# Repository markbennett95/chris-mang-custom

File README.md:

# Custom Dual OD - Chris Mang

Custom dual drive in a 1590BB featuring a Zendrive on one side, and a modified bluesbreaker on the other.

## v1.0.0-build
1590BB encl. Works with `1590BB-2` of the [Dual Effect Order Switching Board](https://github.com/markbennett95/dual-effect-order-switching-board). Zendrive schematic is unchanged, using the "version" switch and a DG412. The Bluesbreaker is a pretty straight up clone with added clean blend.

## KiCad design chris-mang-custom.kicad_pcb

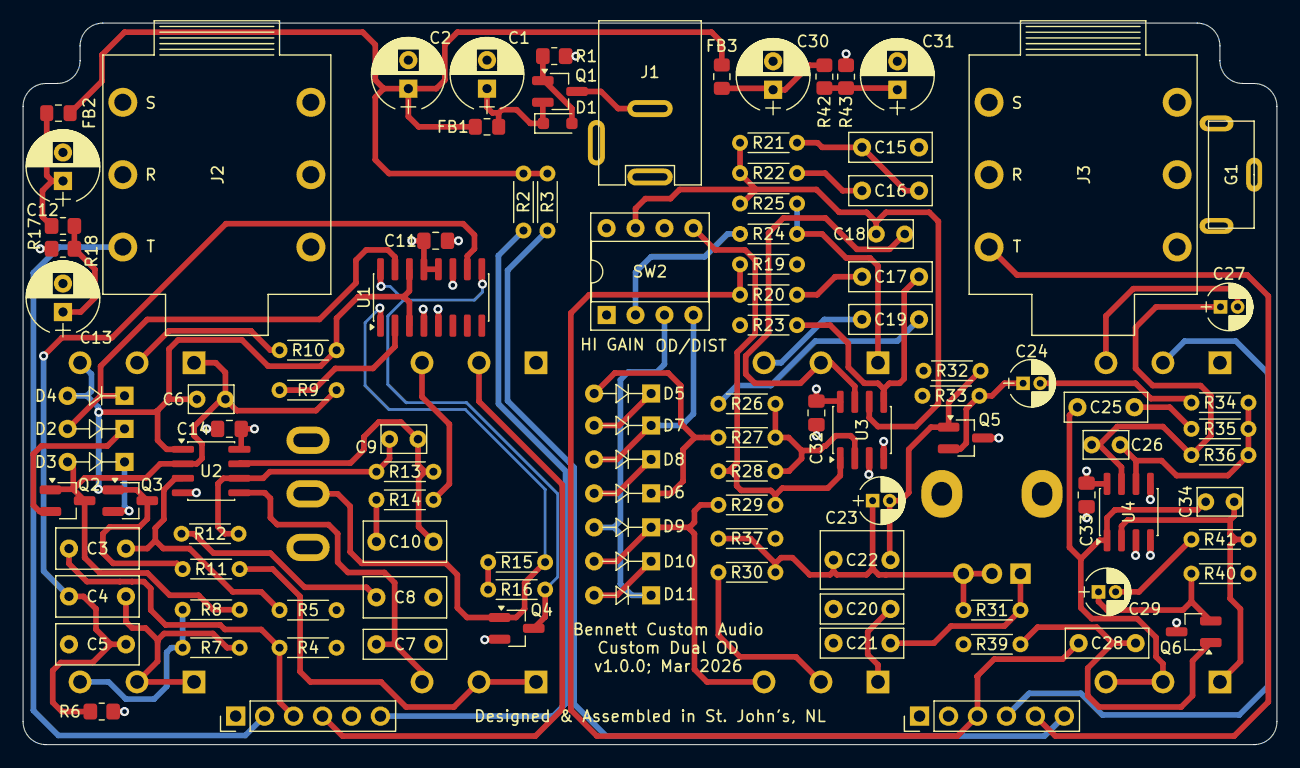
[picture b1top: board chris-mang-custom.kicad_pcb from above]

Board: 4 copper layers, 110.0 x 63.3 mm, 117 parts (1 on the bottom side), 72 nets.

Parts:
C1, C2: 100uF; CP_Radial_D6.3mm_P2.50mm
C3: 0.47u; C_Film_L7.2mm_W3.5mm_P5.00mm
C4, C5: 0.22u; C_Film_L7.2mm_W3.5mm_P5.00mm
C6, C18, C34: 100p; C_Ceramic_L4.0mm_W2.5mm_P2.50mm
C7: 3.3nF; C_Film_L7.2mm_W2.5mm_P5.00mm
C8: 0.22uF; C_Film_L7.2mm_W3.5mm_P5.00mm
C9: 470p; C_Ceramic_L4.0mm_W2.5mm_P2.50mm
C10: 0.47uF; C_Film_L7.2mm_W3.5mm_P5.00mm
C11: 1u; C_0805_2012Metric_Pad1.18x1.45mm_HandSolder
C12, C13, C30, C31: 100u; CP_Radial_D6.3mm_P2.50mm
C14, C32, C33: 100n; C_0805_2012Metric_Pad1.18x1.45mm_HandSolder
C15, C16, C17, C20, C21, C28: 10n; C_Film_L7.2mm_W2.5mm_P5.00mm
C19: 0.1u; C_Film_L7.2mm_W2.5mm_P5.00mm
C22: 1u; C_Film_L7.2mm_W5.00mm_P5.00mm
C23: 1u; CP_Radial_D4.0mm_P1.50mm
C24, C27, C29: 10u; CP_Radial_D4.0mm_P1.50mm
C25: 47n; C_Film_L7.2mm_W2.5mm_P5.00mm
C26: 47p; C_Ceramic_L4.0mm_W2.5mm_P2.50mm
D1: 9V1 Zener; D_SOD-323_HandSoldering
D2, D3, D4, D11: 1N5711; Diode_DO-35_P5.00mm
D5, D6, D7, D8, D9, D10: 1N4148; Diode_DO-35_P5.00mm
FB1, FB2, FB3: FerriteBead_Small; L_0805_2012Metric_Pad1.15x1.40mm_HandSolder
G1: GNDSpring; Keystone_628
J1: Barrel_Jack_Switch; DC_Jack_DC005
J2, J3: AudioJack_TRS; Rean_NYS215
J4, J5: Conn_01x06; Pin_Header_Straight_1x06_Pitch2.54mm
Q1: Q_PMOS_GSD; SOT-23_Handsoldering
Q2, Q3, Q4: 2N7002; SOT-23_Handsoldering
Q5, Q6: BC848C; SOT-23_Handsoldering
R1, R17, R18, R42, R43: 10k; R_0805_2012Metric_Pad1.20x1.40mm_HandSolder
R2, R3: 22k; R_L3.6mm_D1.6mm_P5.00mm_Horizontal
R4: 2.2M; R_L3.6mm_D1.6mm_P5.00mm_Horizontal
R5: 470k; R_L3.6mm_D1.6mm_P5.00mm_Horizontal
R6: 10M; R_0805_2012Metric_Pad1.20x1.40mm_HandSolder
R7, R10, R11, R13, R20, R26, R33, R40, R41: 10k; R_L3.6mm_D1.6mm_P5.00mm_Horizontal
R8, R14, R29: 1k; R_L3.6mm_D1.6mm_P5.00mm_Horizontal
R9: 680k; R_L3.6mm_D1.6mm_P5.00mm_Horizontal
R12: 18k; R_L3.6mm_D1.6mm_P5.00mm_Horizontal
R15, R16, R31, R34, R35, R37: 100k; R_L3.6mm_D1.6mm_P5.00mm_Horizontal
R19, R23, R32, R39: 1M; R_L3.6mm_D1.6mm_P5.00mm_Horizontal
R21: 27k; R_L3.6mm_D1.6mm_P5.00mm_Horizontal
R22: 33k; R_L3.6mm_D1.6mm_P5.00mm_Horizontal
R24: 39k; R_L3.6mm_D1.6mm_P5.00mm_Horizontal
R25: 150k; R_L3.6mm_D1.6mm_P5.00mm_Horizontal
R27, R30: 6.8k; R_L3.6mm_D1.6mm_P5.00mm_Horizontal
R28: 220k; R_L3.6mm_D1.6mm_P5.00mm_Horizontal
R36: 180k; R_L3.6mm_D1.6mm_P5.00mm_Horizontal
RV1: 10kC; R_POT
RV2: 1MA; R_POT
RV3: 50kB; R_POT
RV4, RV8, RV9: 100kA; R_POT
RV5: 100kB; R_POT
RV6: 25kB; R_POT
RV7: 100kA; R_POT_9mm
SW1: SW_SPDT; SW_Toggle_SPDT_SolderLug
SW2: SW_DIP_SPDT_2pos; DIP-8_W7.62mm_Socket
U1: DG412xY; SOIC-16_3.9x9.9mm_P1.27mm
U2: OPA2134; SOIC-8_3.9x4.9mm_P1.27mm
U3: NJM4580; SOIC-8_3.9x4.9mm_P1.27mm
U4: TLV9352; SOIC-8_3.9x4.9mm_P1.27mm

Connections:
+9V: C2.1, FB1.2, FB2.1, FB3.1, R2.2, R3.2
/V+0: J4.6, R2.1
/V+1: J5.6, R3.1
/Zendrive/4.5V: C13.1, R5.1, R17.1, R18.2
/Zendrive/9V: C11.1, C12.1, C14.1, FB2.2, R15.2, R16.2, R17.2, U1.12 (VL), U1.13 (V+), U2.8 (V+)
/Zendrive/Q1D: Q4.3 (D), R16.1, U1.9, U1.16
/Zendrive/Q1G: Q4.1 (G), R15.1, SW1.2 (B), U1.1
/bluesbreaker-return: J5.4, RV8.2
/bluesbreaker-send: C28.1, J5.3, R19.2, R20.1
/bluesbreaker/4.5V: C20.1, C21.1, C31.1, R23.1, R32.1, R37.1, R39.1, R42.1, R43.2, SW2.6 (A), U3.3 (+), U4.3 (+), U4.5 (+)
/bluesbreaker/9V: C30.1, C32.1, C33.1, FB3.2, Q5.3 (C), Q6.3 (C), R42.2, U3.8 (V+), U4.8 (V+)
/bluesbreaker/sw2: R24.1, SW2.2 (D)
/bluesbreaker/sw3: D9.2 (A), D11.1 (K), SW2.3 (C)
/bluesbreaker/sw4: D7.1 (K), D8.2 (A), SW2.4 (D)
/bluesbreaker/sw5: R28.2, R29.1, SW2.5 (B), U3.1
/bluesbreaker/sw7: C18.1, R21.2, R22.2, R25.1, SW2.7 (B), U3.6 (-)
/input_jack: J2.1 (T), J4.2
/output_jack: J3.1 (T), J5.5
/zendrive_return: J4.4, RV4.2
/zendrive_send: C3.1, J4.3, R4.2
Earth: C1.2, C2.2, C5.1, C7.2, C8.1, C11.2, C12.2, C13.2, C14.2, C15.1, C30.2, C31.2, C32.2, C33.2, G1.1, J1.1, J2.2 (R), J2.3 (S), J2.4 (TS), J2.5 (RS), J2.6 (SS), J3.2 (R), J3.3 (S), J3.4 (TS), J3.5 (RS), J3.6 (SS), J4.1, J5.1, Q4.2 (S), R1.1, R4.1, R6.1, R18.1, R19.1, R33.1, R40.1, R43.1, RV4.1, RV8.1, SW1.1 (A), U1.4 (V-), U1.5 (GND), U1.11, U2.4 (V-), U3.4 (V-), U4.4 (V-)
unnamed: C4.1, C5.2, R6.2, U1.10
unnamed: C4.2, R7.1, RV1.1, RV1.2
unnamed: C8.2, R12.1
unnamed: C9.2, C10.1, R13.2, U2.7
unnamed: C10.2, R14.1
unnamed: C15.2, C16.1, R21.1
unnamed: C16.2, R22.1
unnamed: C17.1, R20.2
unnamed: C18.2, RV5.2, U3.7
unnamed: C19.1, RV5.3
unnamed: C19.2, R26.1
unnamed: C20.2, RV6.1
unnamed: C21.2, R31.1, RV7.1
unnamed: C22.1, C23.1, R30.2, R31.2, R37.2, RV7.2, RV7.3
unnamed: C24.2, R34.1
unnamed: C25.1, C34.2, RV9.2, RV9.3, U4.1
unnamed: C25.2, R35.1
unnamed: C26.2, C27.1, R36.2, U4.7
unnamed: C27.2, RV8.3
unnamed: C29.2, R41.1
unnamed: D1.2 (A), Q1.1 (G), R1.2
unnamed: C1.1, D1.1 (K), FB1.1, Q1.2 (S)
unnamed: D2.2 (A), D4.1 (K), U1.15
unnamed: D2.1 (K), Q2.2 (S)
unnamed: C6.1, D3.2 (A), Q2.1 (G), Q2.3 (D), R8.2, R9.1, RV2.1, U2.2 (-)
unnamed: D3.1 (K), Q3.2 (S)
unnamed: C6.2, D4.2 (A), Q3.1 (G), Q3.3 (D), R10.2, R11.1, RV2.3, U1.3, U1.14, U2.1
unnamed: D5.2 (A), D6.1 (K), R27.2
unnamed: D5.1 (K), D7.2 (A)
unnamed: D6.2 (A), D8.1 (K)
unnamed: D9.1 (K), D10.2 (A), R29.2, RV6.3
unnamed: D10.1 (K), D11.2 (A)
unnamed: J1.2, Q1.3 (D)
unnamed: C22.2, C23.2, Q5.1 (B), R32.2
unnamed: C24.1, Q5.2 (E), R33.2
unnamed: C28.2, Q6.1 (B), R39.2
unnamed: C29.1, Q6.2 (E), R40.2
unnamed: R7.2, R8.1, RV1.3
unnamed: R9.2, U1.2
unnamed: R10.1, RV2.2
unnamed: R11.2, RV3.1, RV3.2
unnamed: R14.2, RV4.3
unnamed: R24.2, R25.2, RV5.1
unnamed: R30.1, RV6.2
unnamed: C3.2, R5.2, U2.3 (+)
unnamed: C7.1, RV3.3, U2.5 (+)
unnamed: C9.1, R12.2, R13.1, U2.6 (-)
unnamed: R26.2, R27.1, R28.1, U3.2 (-)
unnamed: C17.2, R23.2, U3.5 (+)
unnamed: C34.1, R41.2, RV9.1, U4.2 (-)
unnamed: C26.1, R34.2, R35.2, R36.1, U4.6 (-)

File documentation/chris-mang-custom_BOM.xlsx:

Value | Qty | Reference | Footprint
100nF | 3 | C14,C32,C33 | Capacitor_SMD:C_0805_2012Metric_Pad1.18x1.45mm_HandSolder
1uF | 1 | C11 | Capacitor_SMD:C_0805_2012Metric_Pad1.18x1.45mm_HandSolder
FerriteBead_Small | 3 | FB1,FB2,FB3 | Inductor_SMD:L_0805_2012Metric_Pad1.15x1.40mm_HandSolder
10k | 5 | R1,R17,R18,R42,R43 | Resistor_SMD:R_0805_2012Metric_Pad1.20x1.40mm_HandSolder
10M | 1 | R6 | Resistor_SMD:R_0805_2012Metric_Pad1.20x1.40mm_HandSolder
9V1 Zener | 1 | D1 | Diode_SMD:D_SOD-323_HandSoldering
Q_PMOS_GSD | 1 | Q1 | Package_TO_SOT_SMD:SOT-23_Handsoldering
BC848C | 2 | Q5,Q6 | Package_TO_SOT_SMD:SOT-23_Handsoldering
2N7002 | 3 | Q2,Q3,Q4 | Package_TO_SOT_SMD:SOT-23_Handsoldering
TLV9352 | 1 | U4 | Package_SO:SOIC-8_3.9x4.9mm_P1.27mm
NJM4580 | 1 | U3 | Package_SO:SOIC-8_3.9x4.9mm_P1.27mm
OPA1642 | 1 | U2 | Package_SO:SOIC-8_3.9x4.9mm_P1.27mm
DG412xY | 1 | U1 | Package_SO:SOIC-16_3.9x9.9mm_P1.27mm
1k | 3 | R8,R14,R29 | bca-footprints:R_L3.6mm_D1.6mm_P5.00mm_Horizontal
6.8k | 2 | R27,R30 | bca-footprints:R_L3.6mm_D1.6mm_P5.00mm_Horizontal
10k | 9 | R7,R10,R11,R13,R20,R26,R33,R40,R41 | bca-footprints:R_L3.6mm_D1.6mm_P5.00mm_Horizontal
18k | 1 | R12 | bca-footprints:R_L3.6mm_D1.6mm_P5.00mm_Horizontal
22k | 2 | R2,R3 | bca-footprints:R_L3.6mm_D1.6mm_P5.00mm_Horizontal
27k | 1 | R21 | bca-footprints:R_L3.6mm_D1.6mm_P5.00mm_Horizontal
33k | 1 | R22 | bca-footprints:R_L3.6mm_D1.6mm_P5.00mm_Horizontal
39k | 1 | R24 | bca-footprints:R_L3.6mm_D1.6mm_P5.00mm_Horizontal
100k | 6 | R15,R16,R31,R34,R35,R37 | bca-footprints:R_L3.6mm_D1.6mm_P5.00mm_Horizontal
150k | 1 | R25 | bca-footprints:R_L3.6mm_D1.6mm_P5.00mm_Horizontal
180k | 1 | R36 | bca-footprints:R_L3.6mm_D1.6mm_P5.00mm_Horizontal
220k | 1 | R28 | bca-footprints:R_L3.6mm_D1.6mm_P5.00mm_Horizontal
470k | 1 | R5 | bca-footprints:R_L3.6mm_D1.6mm_P5.00mm_Horizontal
680k | 1 | R9 | bca-footprints:R_L3.6mm_D1.6mm_P5.00mm_Horizontal
1M | 4 | R19,R23,R32,R39 | bca-footprints:R_L3.6mm_D1.6mm_P5.00mm_Horizontal
2.2M | 1 | R4 | bca-footprints:R_L3.6mm_D1.6mm_P5.00mm_Horizontal
1N4148 | 6 | D5,D6,D7,D8,D9,D10 | bca-footprints:Diode_DO-35_P5.00mm
1N5711 | 4 | D2,D3,D4,D11 | bca-footprints:Diode_DO-35_P5.00mm
47pF | 1 | C26 | bca-footprints:C_Ceramic_L4.0mm_W2.5mm_P2.50mm
100pF | 3 | C6,C18,C34 | bca-footprints:C_Ceramic_L4.0mm_W2.5mm_P2.50mm
470pF | 1 | C9 | bca-footprints:C_Ceramic_L4.0mm_W2.5mm_P2.50mm
3.3nF | 1 | C7 | bca-footprints:C_Film_L7.2mm_W2.5mm_P5.00mm
10nF | 6 | C15,C16,C17,C20,C21,C28 | bca-footprints:C_Film_L7.2mm_W2.5mm_P5.00mm
47nF | 1 | C25 | bca-footprints:C_Film_L7.2mm_W2.5mm_P5.00mm
0.1uF | 1 | C19 | bca-footprints:C_Film_L7.2mm_W2.5mm_P5.00mm
0.22uF | 3 | C4,C5,C8 | bca-footprints:C_Film_L7.2mm_W3.5mm_P5.00mm
0.47uF | 2 | C3,C10 | bca-footprints:C_Film_L7.2mm_W3.5mm_P5.00mm
1uF | 1 | C22 | bca-footprints:C_Film_L7.2mm_W5.00mm_P5.00mm
1uF | 1 | C23 | bca-footprints:CP_Radial_D4.0mm_P1.50mm
10uF | 3 | C24,C27,C29 | bca-footprints:CP_Radial_D4.0mm_P1.50mm
100uF | 6 | C1,C2,C12,C13,C30,C31 | bca-footprints:CP_Radial_D6.3mm_P2.50mm
SW_DIP_SPDT_2pos | 1 | SW2 | bca-footprints:DIP-8_W7.62mm_Socket
AudioJack_TRS | 2 | J2,J3 | bca-footprints:Rean_NYS215
Barrel_Jack_Switch | 1 | J1 | bca-footprints:DC_Jack_DC005
GNDSpring | 1 | G1 | bca-footprints:Keystone_628
10kC | 1 | RV1 | bca-footprints:R_POT
25kB | 1 | RV6 | bca-footprints:R_POT
50kB | 1 | RV3 | bca-footprints:R_POT
100kA | 3 | RV4,RV8,RV9 | bca-footprints:R_POT
100kB | 1 | RV5 | bca-footprints:R_POT
1MA | 1 | RV2 | bca-footprints:R_POT
SW_SPDT | 1 | SW1 | bca-footprints:SW_Toggle_SPDT_SolderLug
100kA | 1 | RV7 | bca-footprints:R_POT_9mm

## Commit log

2026-02-13 finished bd2 schematic
2026-02-17 added bluesbreaker schematic
2026-02-18 first route of PCB
2026-02-26 finalized schematic
2026-03-05 first draft PCB
2026-03-13 generated gerbers
2026-04-26 re-generated gerbers, finalized BOM
